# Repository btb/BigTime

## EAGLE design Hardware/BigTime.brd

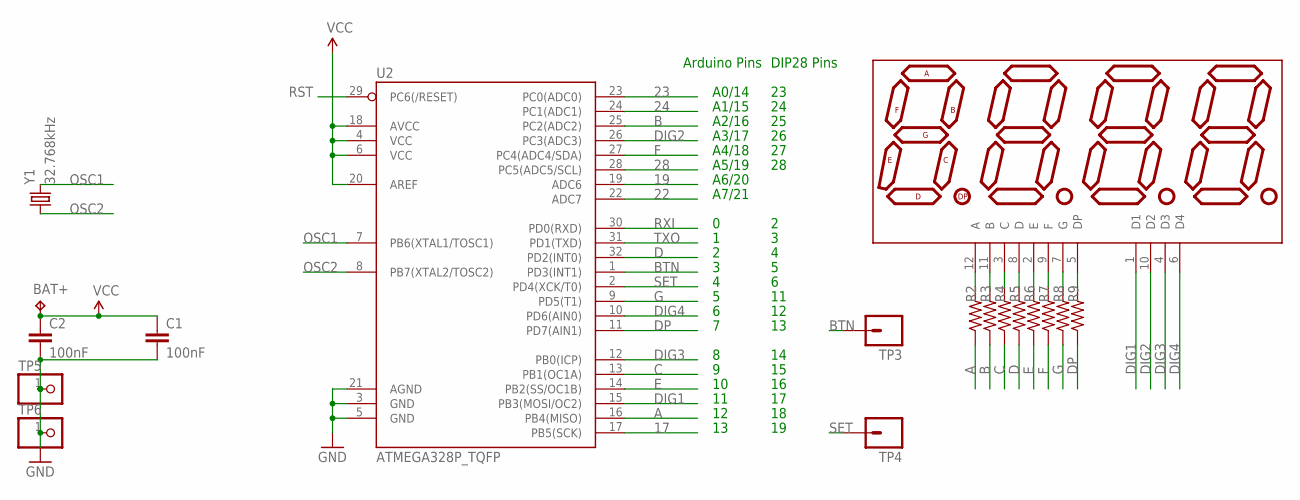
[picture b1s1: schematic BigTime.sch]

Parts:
BAT+: TPTP20R; TP20R
C1, C2: 100nF; C0805
DISP1: 7-SEGMENT-4DIGIT-COUNTER-HP-BUBBLE-SM; DIL12_SM
R2, R3, R4, R5, R6, R7, R8, R9: 330; R0805
TP3, TP4: M01EDGE_CONTACT; WATCHBTN
TP5, TP6: PINHD-1X1CB; 1X01-CLEANBIG
U2: ATMEGA328P_TQFP; TQFP32-08
Y1: 32.768kHz; TC26H

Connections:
17: U2.17 (PB5(SCK))
19: U2.19 (ADC6)
22: U2.22 (ADC7)
23: U2.23 (PC0(ADC0))
24: U2.24 (PC1(ADC1))
28: U2.28 (PC5(ADC5/SCL))
A: R2.1, U2.16 (PB4(MISO))
A': DISP1.12 (A), R2.2
B: R3.1, U2.25 (PC2(ADC2))
B': DISP1.11 (B), R3.2
BTN: TP3.1, U2.1 (PD3(INT1))
C: R4.1, U2.13 (PB1(OC1A))
C': DISP1.3 (C), R4.2
D: R5.1, U2.32 (PD2(INT0))
D': DISP1.8 (D), R5.2
DIG1: DISP1.1 (D1), U2.15 (PB3(MOSI/OC2))
DIG2: DISP1.10 (D2), U2.26 (PC3(ADC3))
DIG3: DISP1.4 (D3), U2.12 (PB0(ICP))
DIG4: DISP1.6 (D4), U2.10 (PD6(AIN0))
DP: R9.1, U2.11 (PD7(AIN1))
DP': DISP1.5 (DP), R9.2
E: R6.1, U2.14 (PB2(SS/OC1B))
E': DISP1.2 (E), R6.2
F: R7.1, U2.27 (PC4(ADC4/SDA))
F': DISP1.9 (F), R7.2
G: R8.1, U2.9 (PD5(T1))
G': DISP1.7 (G), R8.2
GND: C1.2, C2.2, TP5.1, TP6.1, U2.3 (GND), U2.5 (GND), U2.21 (AGND)
OSC1: U2.7 (PB6(XTAL1/TOSC1)), Y1.2
OSC2: U2.8 (PB7(XTAL2/TOSC2)), Y1.1
RST: U2.29 (PC6(/RESET))
RXI: U2.30 (PD0(RXD))
SET: TP4.1, U2.2 (PD4(XCK/T0))
TXO: U2.31 (PD1(TXD))
VCC: BAT+.TP, C1.1, C2.1, U2.4 (VCC), U2.6 (VCC), U2.18 (AVCC), U2.20 (AREF)

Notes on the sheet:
A0/14
A1/15
A2/16
A3/17
A4/18
A5/19
Arduino Pins
DIP28 Pins
A6/20
A7/21

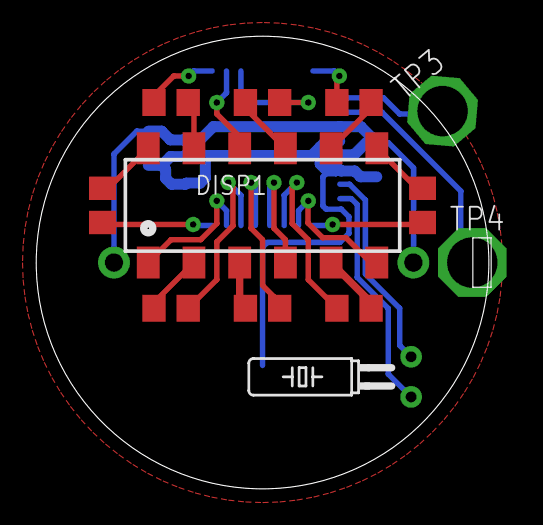
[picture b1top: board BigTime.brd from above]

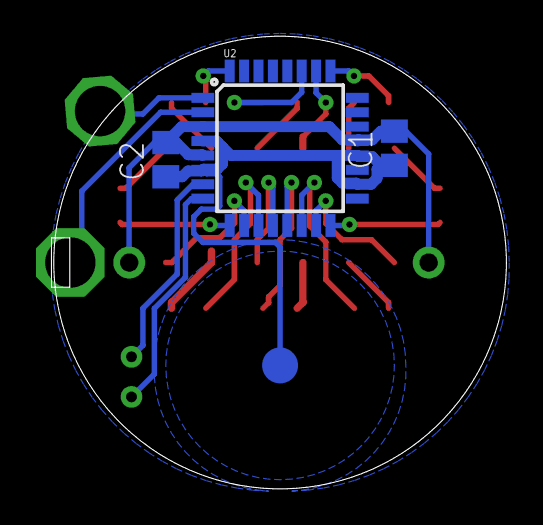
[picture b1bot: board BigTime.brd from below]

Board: 2 copper layers, 25.3 x 25.1 mm, 18 parts (4 on the bottom side), 26 nets.

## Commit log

2016-06-16 replace LED with bubble display
2016-06-17 Switch LED to Bubble display
2016-06-17 Correct polarity for letters
2016-06-25 Remove color setting code
2016-06-25 Show time on startup
2016-06-25 Convert to time_t
2016-06-25 clean up
2016-06-25 implement date
2016-06-25 debug print is 24hr
2016-06-27 use the SevSeg library
2016-06-27 State machine for time/date/secs display
    move display code to main loop.
    Use Time library as rtc, sync with crystal every 8s
2016-06-27 use define for pins
2016-06-28 Implement settings
2016-06-28 add set button, reroute pub
2016-06-28 reset year if held down for 10 secs
2016-06-28 use Bounce2 library for debouncing
2016-06-28 Sync system time to crystal when waking up between ticks
2016-06-29 more efficient pin arrangement
2016-06-30 debounce the button interrupt
    don't let state change even if debDisp is high.
2016-07-01 rearrange pins, start fitting to size
2016-07-03 fit 1" footprint
2016-07-04 tweak
2016-07-07 bigger components, no pullup on reset
2016-07-19 Add new board for 45 degree button position
2016-07-19 routing
2016-07-19 fix location of bStop for battery
2016-07-20 update pin numbers
2016-08-04 change to 0805 capacitor
2016-08-09 Change board radius to .495 inch
2016-08-09 reposition disp button pad
2016-08-10 more button work
2016-08-10 rename back to BigTime
2016-08-10 move crystal and ground pads
2019-01-13 Add pins for breadboard version
2019-01-13 use TimeLib.h
2019-01-13 note which version of sevseg we need
2019-01-20 increase display time
2019-01-24 Reroute pins
    Can't use A6 and A7 as digital outs
    Use bigger traces and more spacing
2019-01-29 redesign again
    smaller battery, move ic to back, crystal to front, remap pins

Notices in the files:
parts and their libraries:
SparkFun-DigitalIC: Licensing: CC v3.0 Share-Alike You are welcome to use this library for commercial purposes.
